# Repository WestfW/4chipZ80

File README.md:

# 4chipZ80
Z80 system using ATmega as IO/boot controller.  4 chips total.
---
This is a minimalist Z80 system based on a breadboard design by "Just4Fun" at hackaday.io:
https://hackaday.io/project/19000

My main contribution so far is the creation of a PCB, for a more permenant construction than the original breadboard.
This involved converting the printed schematic to an EAGLE version, as well as laying out the PCB. 

This project has won an **"Anything Goes" HackaDay prize** (for Just4Fun), and at this point has been built by a relatively impressive number of people in a rather impressive variety of different ways (not all of them using this PCB.)

The initial V1 PCB was sent for fabrication at PCBWAY.COM on 20170111.  It's been received, reviewed, and built (fully built as of 20170202), and it works, but it has some bugs:

 1. Short of I2C line to Ground plain.
 2. Missing pullup (IORQ) and pulldown (RESET) resistors.
 3. Rx/Tx swapped on serial connection.
 
Fixing these manually results in a working board.  It's not clear that the pull-resistors are needed.

There are now several versions of the EAGLE Schematic/PCB design posted here:

 1. Gerbers-v1bad.Z80-4chip-PCBWAY-BAD.\* - the design as sent to PCBWAY, complete with errors (except that the errors are "marked.")
With hand-done re-work, this design is known to work.  See the notes in the "To-Do" layer of the board, and the assorted "fix\*" files in that directory.
 1. Z80-4chip-v2.1.\* is the "corrected" design.  It has the fixes for the known bugs.  It also features a clarified (multi-sheet) schematic, *BUT* I have not personally fabbed or tested it, but several people on Hackaday.io have built V2 boards and say that they work.
 2. Z80-4chip-v3.\* Adds sockets for I2C EEPROM "Floppy Disks" that should permit use of CP/M and perhaps other Operating Systems.  Just4Fun has implemented the CP/M and QP/M BIOS and etc.  This has also not yet been fabbed or tested (but I have a volunteer!)  (Also Gerbers-V3/\* has pre-made geber files.)

I don't know if I'll be sending the "new" design(s) to actually be built.  A guy can only use so many Z80 boards, and I'm not up for being "in business."  I'll try to keep this update if other people use the design successfully.

Potential users may want to note that the original developer of the 4-chip Z80 system (Just4Fun) has published a new and improved version of the design that includes a PCB, at https://hackaday.io/project/159973

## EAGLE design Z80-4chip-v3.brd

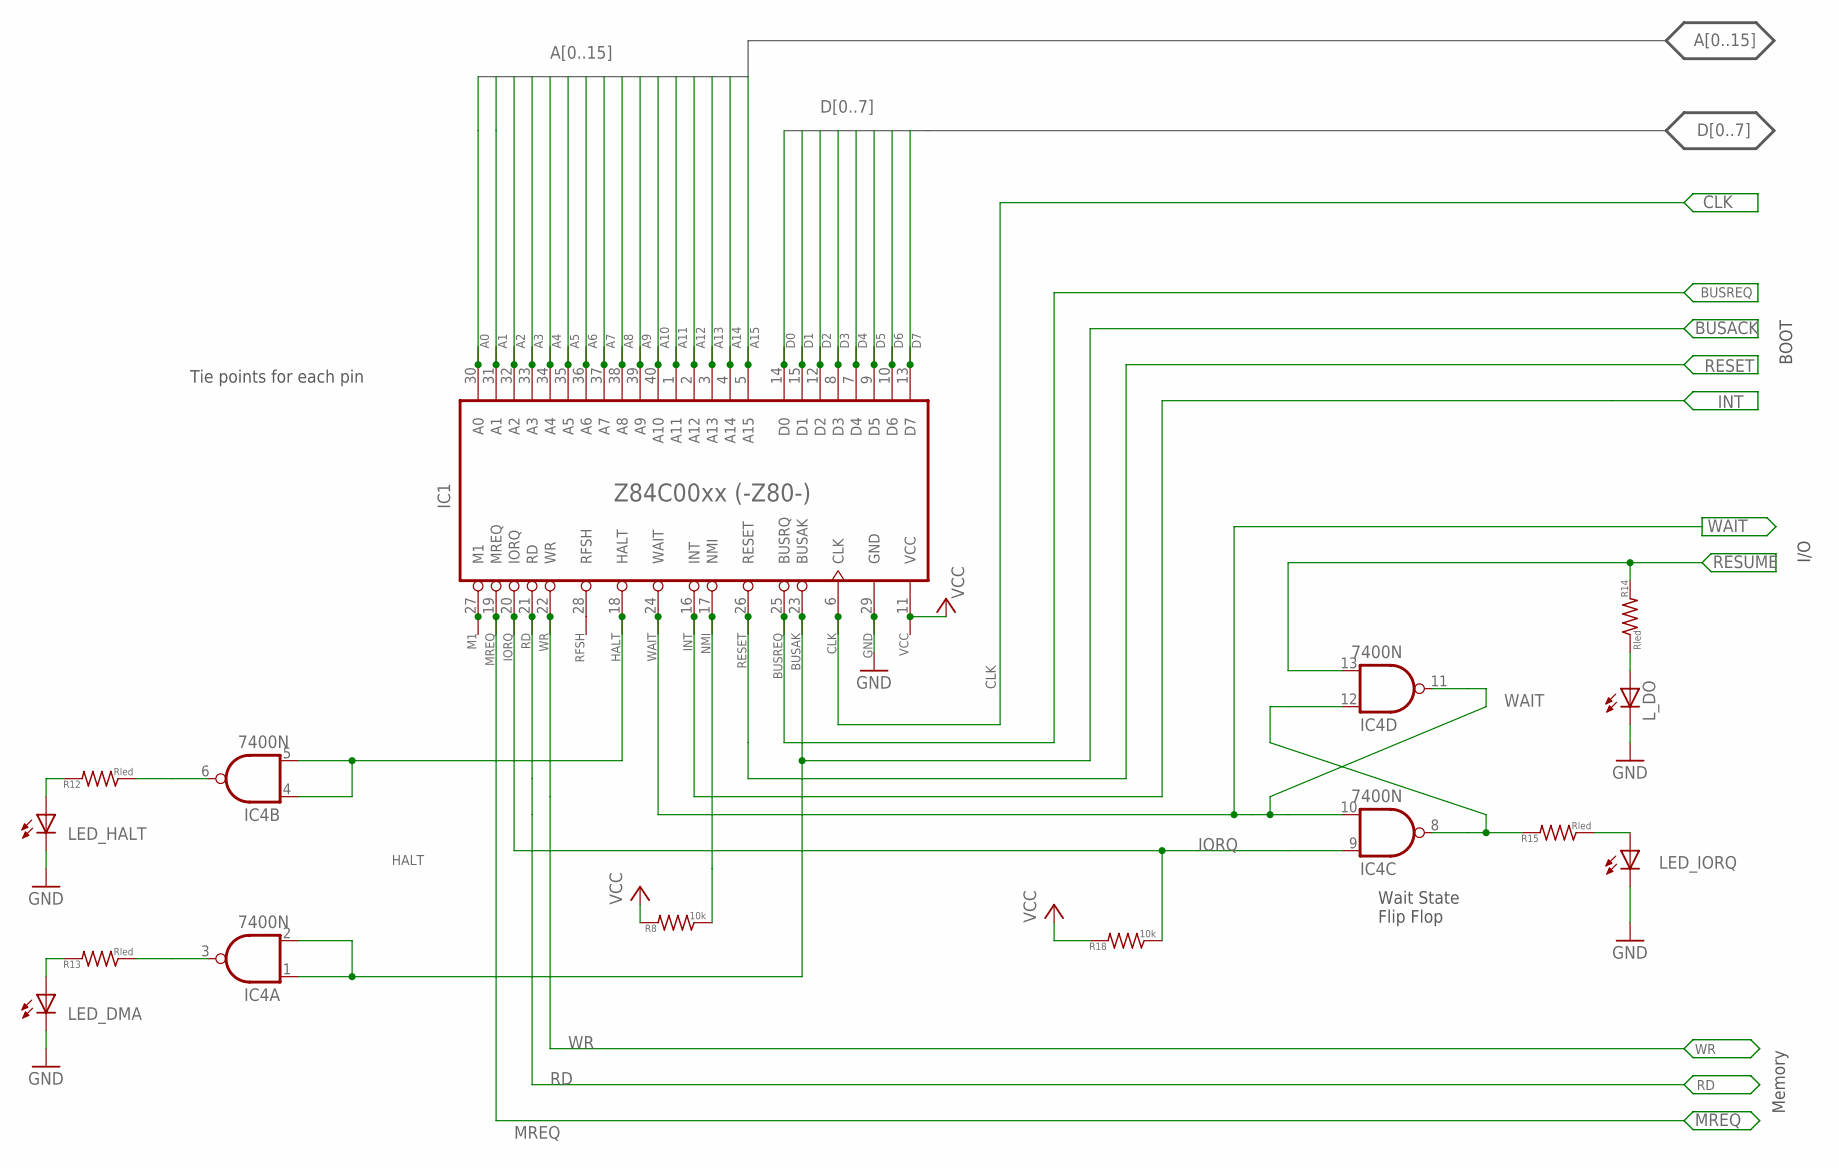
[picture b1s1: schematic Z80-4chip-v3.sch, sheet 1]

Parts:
A0, A1, A2, A3, A4, A5, A6, A7, A8, A9, A10, A11, A12, A13, A14, A15: WIRE-VIA8; VIA8
BUSAK: WIRE-VIA8; VIA8
BUSREQ: WIRE-VIA8; VIA8
CLK: WIRE-VIA8; VIA8
D0, D1, D2, D3, D4, D5, D6, D7: WIRE-VIA8; VIA8
GND: WIRE-VIA8; VIA8
HALT: WIRE-VIA8; VIA8
IC1: Z84C00xx (-Z80-); DIL40
IC4: 7400N; DIL14
INT: WIRE-VIA8; VIA8
IORQ: WIRE-VIA8; VIA8
LED_DMA: LED3MM
LED_HALT: LED3MM
LED_IORQ: LED3MM
L_DO: LED3MM
M1: WIRE-VIA8; VIA8
MREQ: WIRE-VIA8; VIA8
NMI: WIRE-VIA8; VIA8
R8, R18: 10k; 0204/5
R12, R13, R14, R15: Rled; 0204/5
RD: WIRE-VIA8; VIA8
RESET: WIRE-VIA8; VIA8
RFSH: WIRE-VIA8; VIA8
VCC: WIRE-VIA8; VIA8
WAIT: WIRE-VIA8; VIA8
WR: WIRE-VIA8; VIA8

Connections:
A0: A0.P$1, IC1.30 (A0); also elsewhere on the board
A1: A1.P$1, IC1.31 (A1); also elsewhere on the board
A2: A2.P$1, IC1.32 (A2); also elsewhere on the board
A3: A3.P$1, IC1.33 (A3); also elsewhere on the board
A4: A4.P$1, IC1.34 (A4); also elsewhere on the board
A5: A5.P$1, IC1.35 (A5); also elsewhere on the board
A6: A6.P$1, IC1.36 (A6); also elsewhere on the board
A7: A7.P$1, IC1.37 (A7); also elsewhere on the board
A8: A8.P$1, IC1.38 (A8); also elsewhere on the board
A9: A9.P$1, IC1.39 (A9); also elsewhere on the board
A10: A10.P$1, IC1.40 (A10); also elsewhere on the board
A11: A11.P$1, IC1.1 (A11); also elsewhere on the board
A12: A12.P$1, IC1.2 (A12); also elsewhere on the board
A13: A13.P$1, IC1.3 (A13); also elsewhere on the board
A14: A14.P$1, IC1.4 (A14); also elsewhere on the board
A15: A15.P$1, IC1.5 (A15); also elsewhere on the board
BUSACK: BUSAK.P$1, IC1.23 (BUSAK), IC4.1 (I0), IC4.2 (I1); also elsewhere on the board
BUSREQ: BUSREQ.P$1, IC1.25 (BUSRQ); also elsewhere on the board
CLK: CLK.P$1, IC1.6 (CLK); also elsewhere on the board
D0: D0.P$1, IC1.14 (D0); also elsewhere on the board
D1: D1.P$1, IC1.15 (D1); also elsewhere on the board
D2: D2.P$1, IC1.12 (D2); also elsewhere on the board
D3: D3.P$1, IC1.8 (D3); also elsewhere on the board
D4: D4.P$1, IC1.7 (D4); also elsewhere on the board
D5: D5.P$1, IC1.9 (D5); also elsewhere on the board
D6: D6.P$1, IC1.10 (D6); also elsewhere on the board
D7: D7.P$1, IC1.13 (D7); also elsewhere on the board
GND: GND.P$1, IC1.29 (GND), LED_DMA.K (C), LED_HALT.K (C), LED_IORQ.K (C), L_DO.K (C); also elsewhere on the board
HALT: HALT.P$1, IC1.18 (HALT), IC4.4 (I0), IC4.5 (I1)
INT: IC1.16 (INT), INT.P$1; also elsewhere on the board
IORQ: IC1.20 (IORQ), IC4.9 (I0), IORQ.P$1, R18.1
MREQ: IC1.19 (MREQ), MREQ.P$1; also elsewhere on the board
unnamed: IC1.27 (M1), M1.P$1
unnamed: IC4.6 (O), R12.1
unnamed: IC4.3 (O), R13.1
unnamed: LED_HALT.A, R12.2
unnamed: LED_DMA.A, R13.2
unnamed: L_DO.A, R14.1
unnamed: LED_IORQ.A, R15.1
unnamed: IC1.28 (RFSH), RFSH.P$1
unnamed: IC4.8 (O), IC4.12 (I0), R15.2
NMI: IC1.17 (NMI), NMI.P$1, R8.1
RD: IC1.21 (RD), RD.P$1; also elsewhere on the board
RESET: IC1.26 (RESET), RESET.P$1; also elsewhere on the board
RESUME: IC4.13 (I1), R14.2; also elsewhere on the board
VCC: IC1.11 (VCC), R8.2, R18.2, VCC.P$1; also elsewhere on the board
WAIT: IC1.24 (WAIT), IC4.10 (I1), IC4.11 (O), WAIT.P$1; also elsewhere on the board
WR: IC1.22 (WR), WR.P$1; also elsewhere on the board

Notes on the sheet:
Tie points for each pin
Memory
I/O
BOOT
Wait State Flip Flop

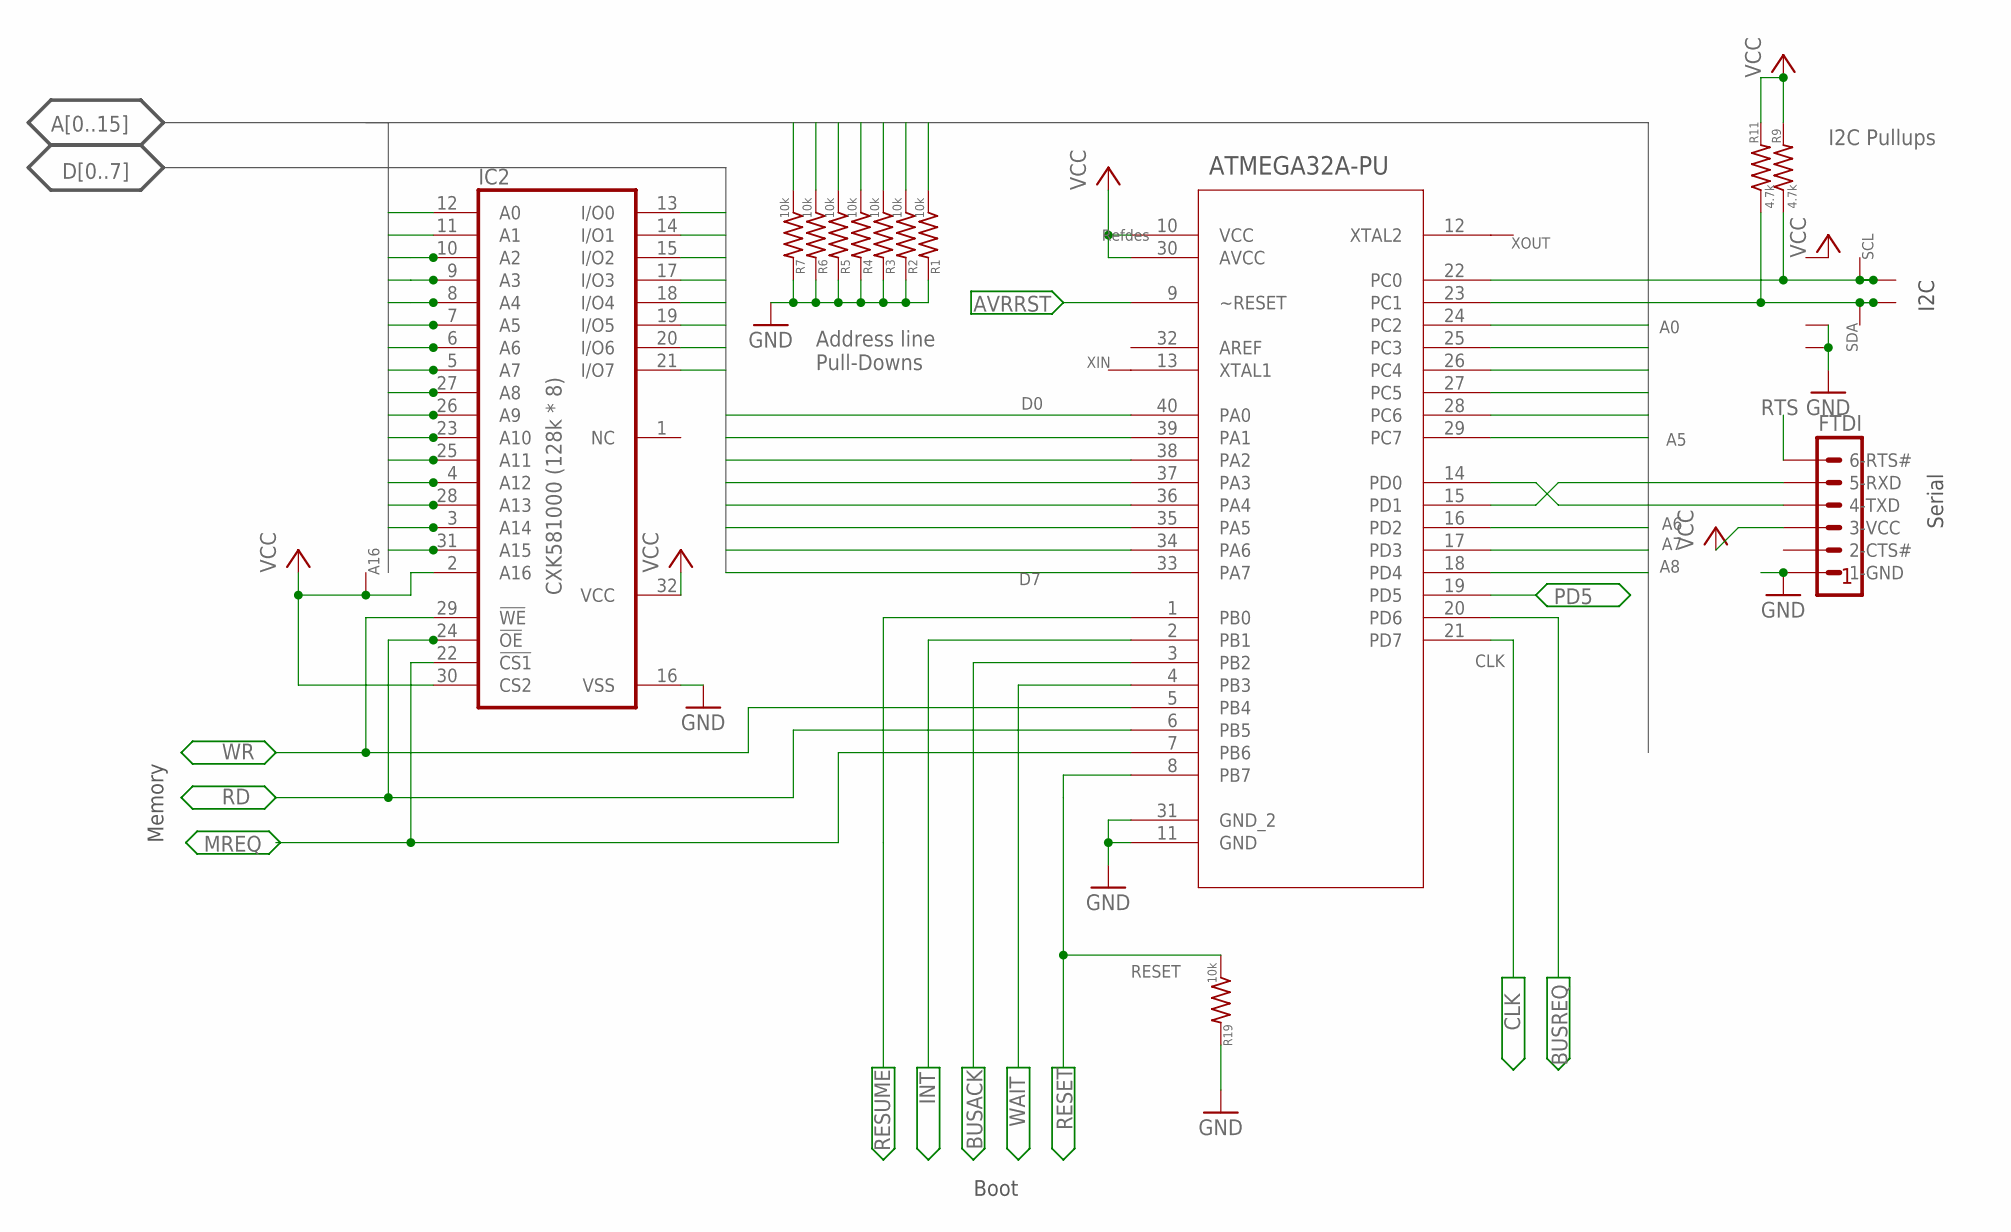
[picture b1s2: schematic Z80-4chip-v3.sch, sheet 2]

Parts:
A16: WIRE-VIA8; VIA8
FTDI: FTDI-TTL232R; MA06-1
I2CG, I2CGND, I2CV: WIRE-R10; VIA10
IC2: CXK581000 (128k * 8); DIL32
R1, R2, R3, R4, R5, R6, R7, R19: 10k; 0204/5
R9, R11: 4.7k; 0204/5
SCL: WIRE-R10; VIA10
SDA: WIRE-R10; VIA10
U1: ATMEGA32A-PU; DIP254P1524X482-40
W1, W2: WIRE-VIA8; VIA8
XIN: WIRE-VIA8; VIA8
XOUT: WIRE-VIA8; VIA8

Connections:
A0: IC2.12 (A0), U1.24 (PC2); also elsewhere on the board
A1: IC2.11 (A1), U1.25 (PC3); also elsewhere on the board
A2: IC2.10 (A2), U1.26 (PC4); also elsewhere on the board
A3: IC2.9 (A3), U1.27 (PC5); also elsewhere on the board
A4: IC2.8 (A4), U1.28 (PC6); also elsewhere on the board
A5: IC2.7 (A5), U1.29 (PC7); also elsewhere on the board
A6: IC2.6 (A6), U1.16 (PD2); also elsewhere on the board
A7: IC2.5 (A7), U1.17 (PD3); also elsewhere on the board
A8: IC2.27 (A8), U1.18 (PD4); also elsewhere on the board
A9: IC2.26 (A9), R1.1; also elsewhere on the board
A10: IC2.23 (A10), R2.1; also elsewhere on the board
A11: IC2.25 (A11), R3.1; also elsewhere on the board
A12: IC2.4 (A12), R4.1; also elsewhere on the board
A13: IC2.28 (A13), R5.1; also elsewhere on the board
A14: IC2.3 (A14), R6.1; also elsewhere on the board
A15: IC2.31 (A15), R7.1; also elsewhere on the board
AVRRST: U1.9 (~RESET); also elsewhere on the board
BUSACK: U1.3 (PB2); also elsewhere on the board
BUSREQ: U1.20 (PD6); also elsewhere on the board
CLK: U1.21 (PD7); also elsewhere on the board
D0: IC2.13 (I/O0), U1.40 (PA0); also elsewhere on the board
D1: IC2.14 (I/O1), U1.39 (PA1); also elsewhere on the board
D2: IC2.15 (I/O2), U1.38 (PA2); also elsewhere on the board
D3: IC2.17 (I/O3), U1.37 (PA3); also elsewhere on the board
D4: IC2.18 (I/O4), U1.36 (PA4); also elsewhere on the board
D5: IC2.19 (I/O5), U1.35 (PA5); also elsewhere on the board
D6: IC2.20 (I/O6), U1.34 (PA6); also elsewhere on the board
D7: IC2.21 (I/O7), U1.33 (PA7); also elsewhere on the board
GND: FTDI.1 (1-GND), I2CG.P$1, I2CGND.P$1, IC2.16 (VSS), R1.2, R2.2, R3.2, R4.2, R5.2, R6.2, R7.2, R19.2, U1.11 (GND), U1.31 (GND_2); also elsewhere on the board
INT: U1.2 (PB1); also elsewhere on the board
MREQ: IC2.22 (!CS1), U1.7 (PB6); also elsewhere on the board
unnamed: FTDI.5 (5-RXD), U1.15 (PD1)
unnamed: FTDI.4 (4-TXD), U1.14 (PD0)
unnamed: U1.13 (XTAL1), XIN.P$1
unnamed: U1.12 (XTAL2), XOUT.P$1
PD5: U1.19 (PD5); also elsewhere on the board
RD: IC2.24 (!OE), U1.6 (PB5); also elsewhere on the board
RESET: R19.1, U1.8 (PB7); also elsewhere on the board
RESUME: U1.1 (PB0); also elsewhere on the board
RTS: FTDI.6 (6-RTS#); also elsewhere on the board
SCL: R9.1, SCL.P$1, U1.22 (PC0), W1.P$1; also elsewhere on the board
SDA: R11.1, SDA.P$1, U1.23 (PC1), W2.P$1; also elsewhere on the board
VCC: A16.P$1, FTDI.3 (3-VCC), I2CV.P$1, IC2.2 (A16), IC2.30 (CS2), IC2.32 (VCC), R9.2, R11.2, U1.10 (VCC), U1.30 (AVCC); also elsewhere on the board
WAIT: U1.4 (PB3); also elsewhere on the board
WR: IC2.29 (!WE), U1.5 (PB4); also elsewhere on the board

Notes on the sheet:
I2C Pullups
Address line Pull-Downs
I2C
Memory
Boot
Serial

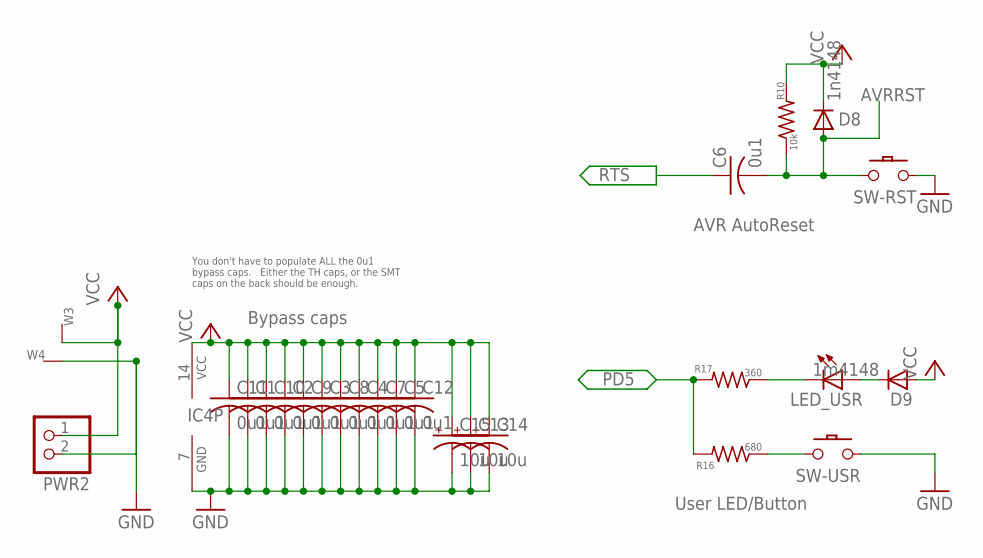
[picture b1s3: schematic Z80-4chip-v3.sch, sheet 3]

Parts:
C1, C2, C3, C4, C5, C6, C7: 0u1; C050-024X044
C8, C9, C10, C11, C12: 0u1; C1206
C13, C14, C15: 10u; E2,5-6
D8: 1n4148; DO35-5
D9: 1m4148; DO35-5
IC4: 7400N; DIL14
LED_USR: LED3MM
PWR2: JST_2PIN-THM; JST-PH-2-THM
R10: 10k; 0204/5
R16: 680; 0204/5
R17: 360; 0204/5
SW-RST: SW-PB2/; SW-PB
SW-USR: SW-PB2L; SW-PB
W3, W4: WIRE-R10; VIA10

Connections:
AVRRST: C6.2, D8.A, R10.1, SW-RST.3; also elsewhere on the board
GND: C1.2, C2.2, C3.2, C4.2, C5.2, C7.2, C8.2, C9.2, C10.2, C11.2, C12.2, C13.-, C14.-, C15.-, IC4.7 (GND), PWR2.2 (1), SW-RST.2, SW-RST.5 (GND), SW-USR.2, SW-USR.5 (GND), W4.P$1; also elsewhere on the board
unnamed: LED_USR.K (C), R17.1
unnamed: D9.C, LED_USR.A
unnamed: R16.1, SW-USR.4
PD5: R16.2, R17.2; also elsewhere on the board
RTS: C6.1; also elsewhere on the board
VCC: C1.1, C2.1, C3.1, C4.1, C5.1, C7.1, C8.1, C9.1, C10.1, C11.1, C12.1, C13.+, C14.+, C15.+, D8.C, D9.A, IC4.14 (VCC), PWR2.1 (2), R10.2, W3.P$1; also elsewhere on the board

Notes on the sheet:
Bypass caps
You don't have to populate ALL the 0u1 bypass caps. Either the TH caps, or the SMT caps on the back should be enough.
AVR AutoReset
User LED/Button

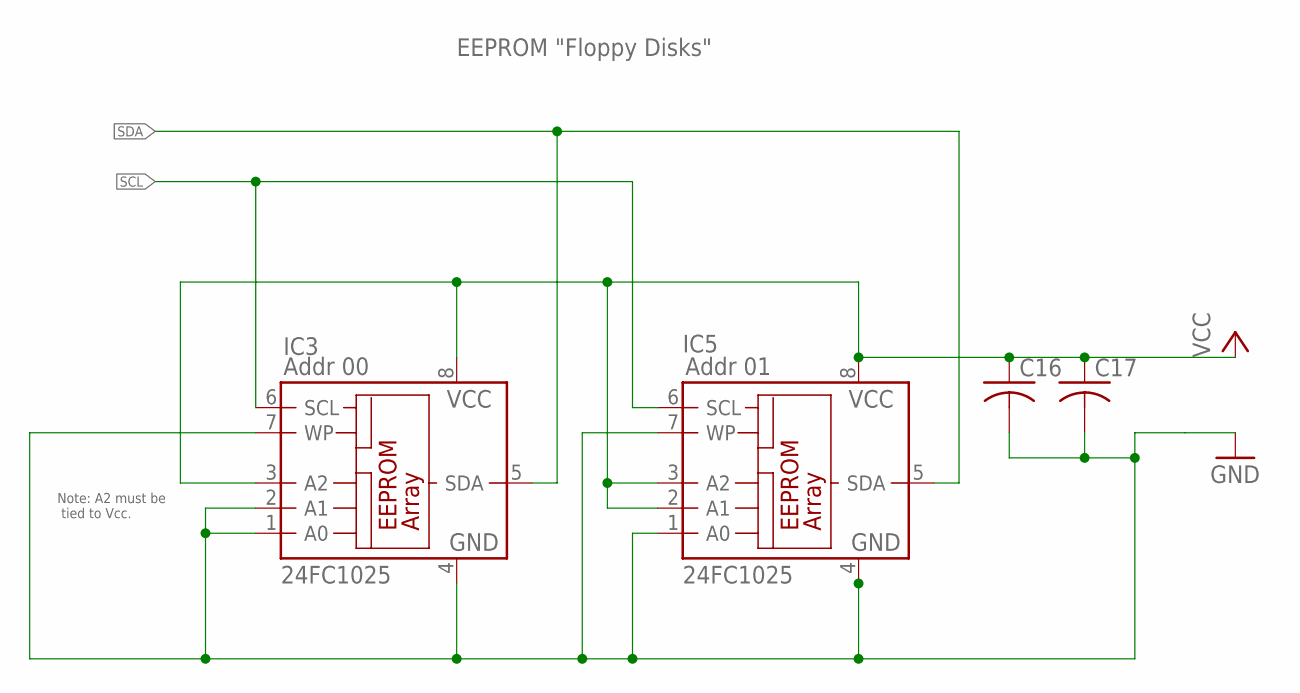
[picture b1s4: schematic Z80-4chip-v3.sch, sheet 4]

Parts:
C16, C17: C-US-5MM; C050-024X044
IC3, IC5: 24FC1025; DIL8

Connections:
GND: C16.2, C17.2, IC3.1 (A0), IC3.2 (A1), IC3.4 (GND), IC3.7 (WP), IC5.1 (A0), IC5.4 (GND), IC5.7 (WP); also elsewhere on the board
SCL: IC3.6 (SCL), IC5.6 (SCL); also elsewhere on the board
SDA: IC3.5 (SDA), IC5.5 (SDA); also elsewhere on the board
VCC: C16.1, C17.1, IC3.3 (A2), IC3.8 (VCC), IC5.2 (A1), IC5.3 (A2), IC5.8 (VCC); also elsewhere on the board

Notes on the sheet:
Addr 00
Addr 01
EEPROM "Floppy Disks"
Note: A2 must be tied to Vcc.

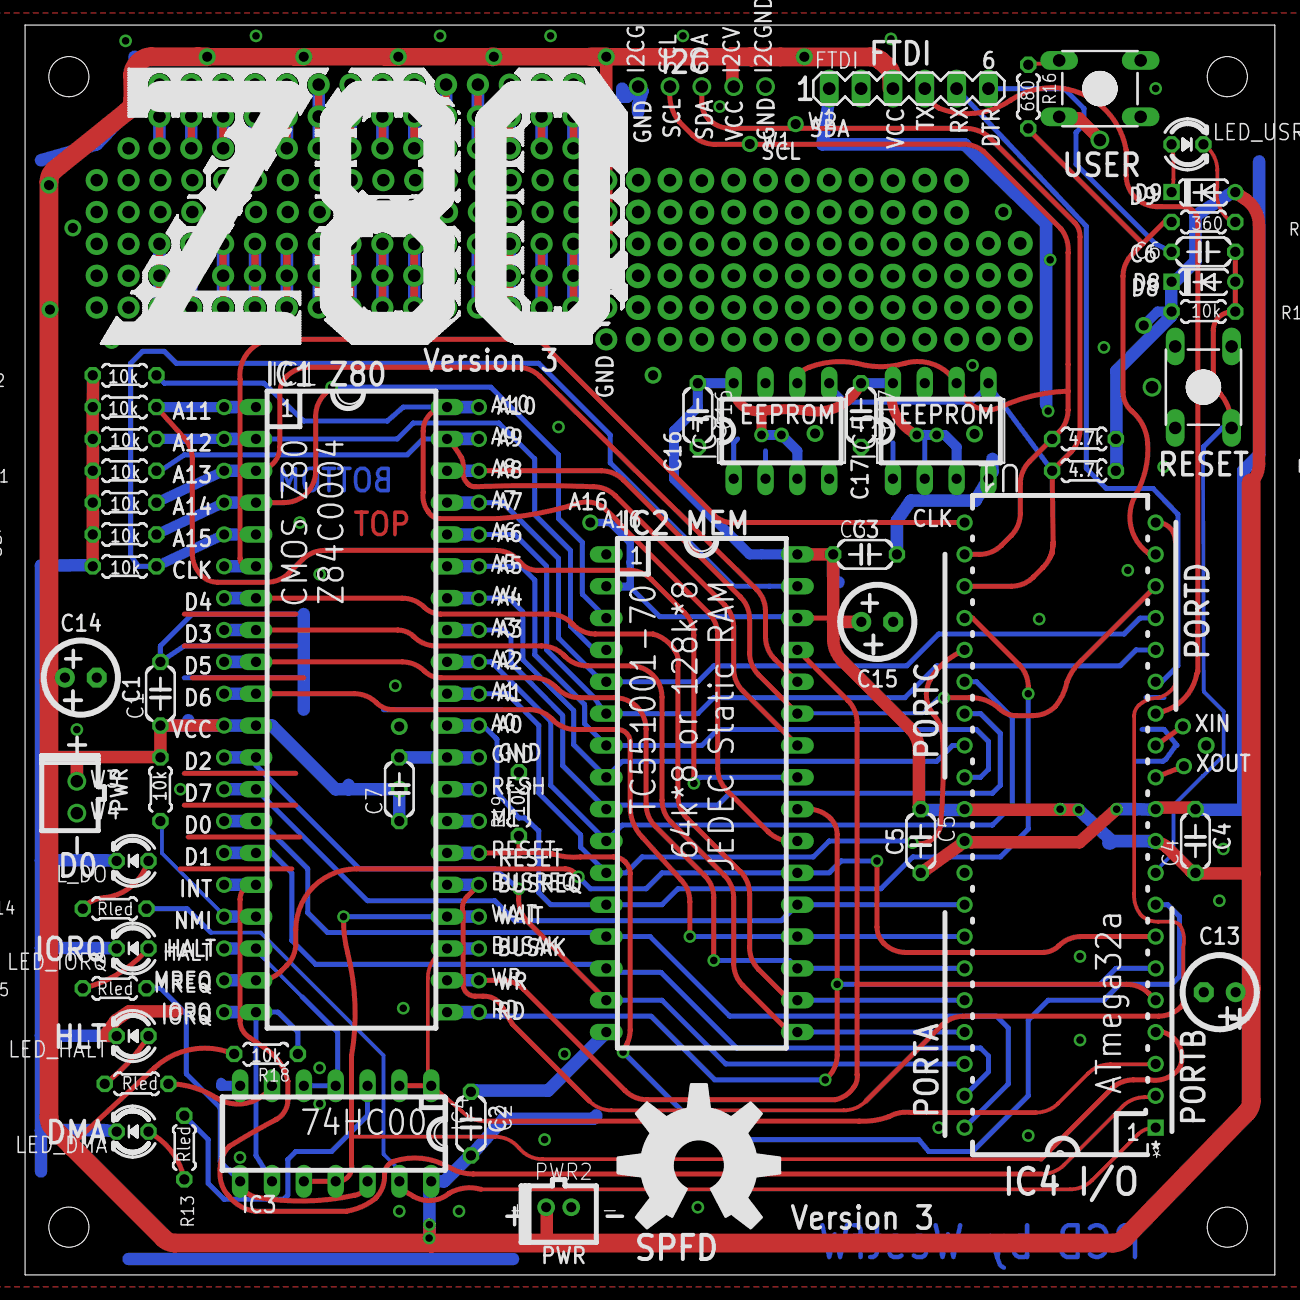
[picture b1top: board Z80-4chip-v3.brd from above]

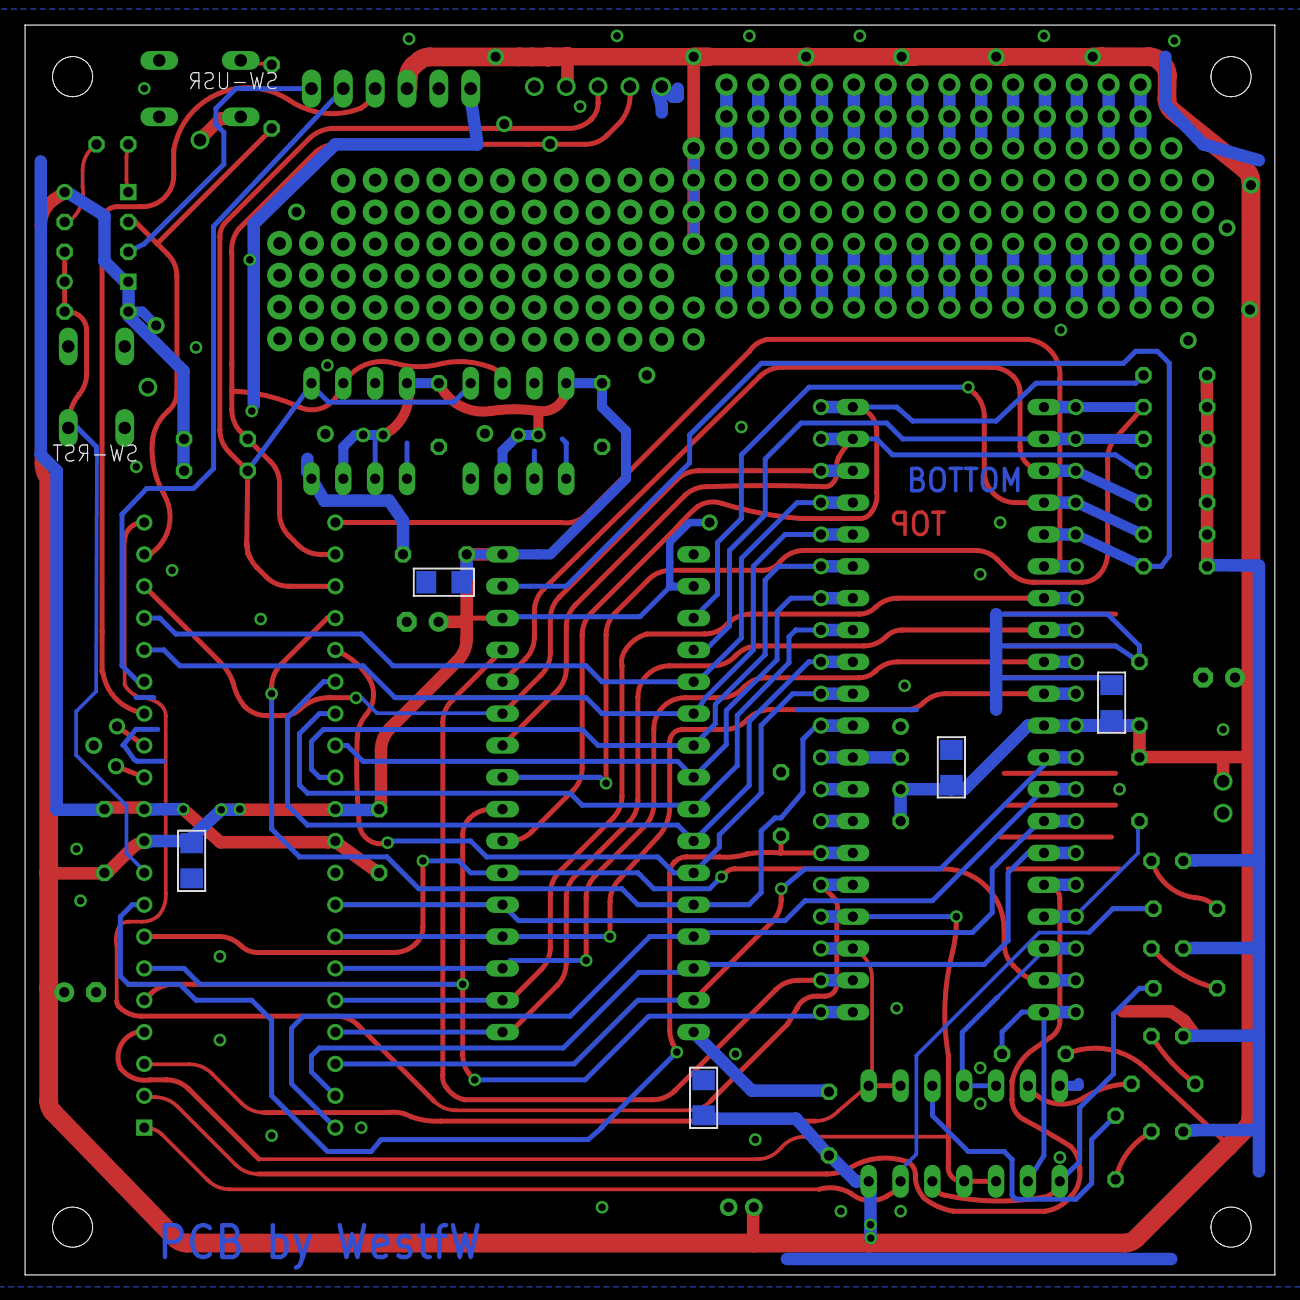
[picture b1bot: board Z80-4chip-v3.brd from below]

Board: 2 copper layers, 99.7 x 99.7 mm, 105 parts (5 on the bottom side), 60 nets.

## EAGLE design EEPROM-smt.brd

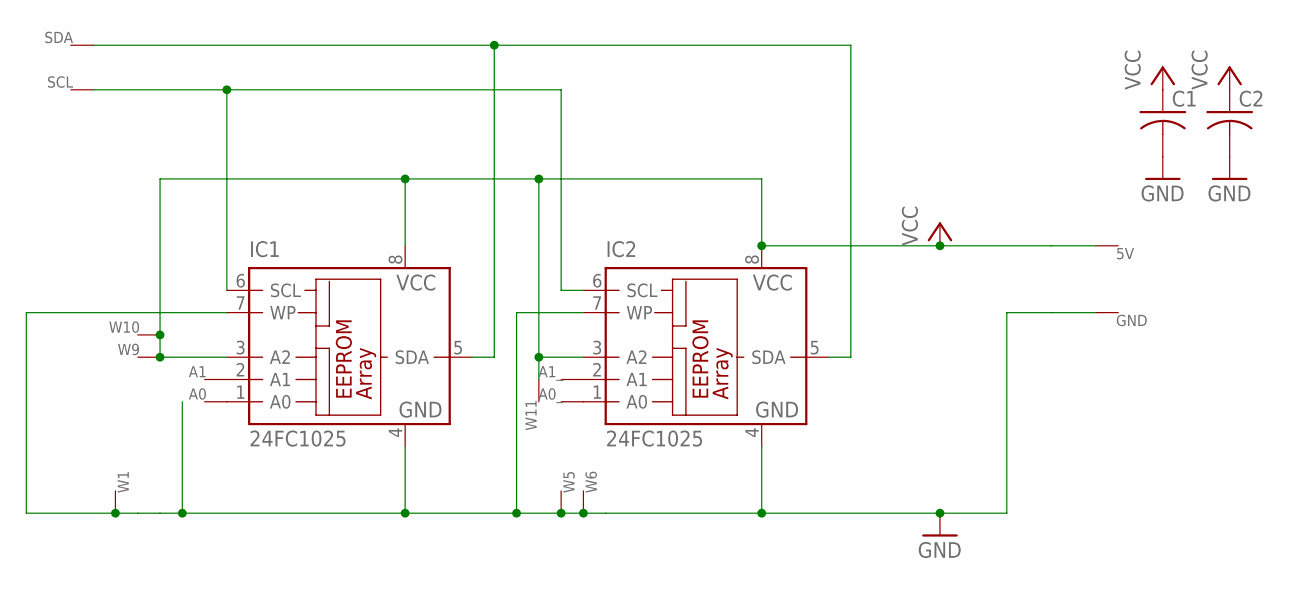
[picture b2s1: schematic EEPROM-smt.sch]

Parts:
5V: WIRE-VIA8; VIA8
A0, A0_, A1, A1_: WIRE-R6; VIA6
C1, C2: C-USC0805; C0805
GND: WIRE-VIA8; VIA8
IC1, IC2: 24FC1025; SO-08
SCL: WIRE-VIA8; VIA8
SDA: WIRE-VIA8; VIA8
W1, W5, W6, W9, W10, W11: WIRE-VIA8; VIA8

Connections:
GND: C1.2, C2.2, GND.P$1, IC1.4 (GND), IC1.7 (WP), IC2.4 (GND), IC2.7 (WP), W1.P$1, W5.P$1, W6.P$1
unnamed: A1.P$1, IC1.2 (A1)
unnamed: A0.P$1, IC1.1 (A0)
unnamed: IC1.6 (SCL), IC2.6 (SCL), SCL.P$1
unnamed: IC1.5 (SDA), IC2.5 (SDA), SDA.P$1
unnamed: A1_.P$1, IC2.2 (A1)
unnamed: A0_.P$1, IC2.1 (A0)
VCC: 5V.P$1, C1.1, C2.1, IC1.3 (A2), IC1.8 (VCC), IC2.3 (A2), IC2.8 (VCC), W9.P$1, W10.P$1, W11.P$1

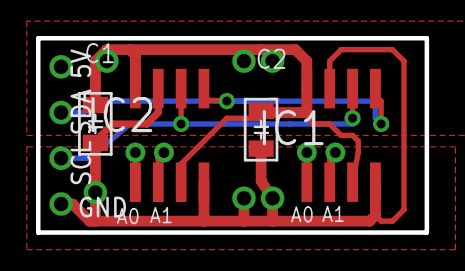
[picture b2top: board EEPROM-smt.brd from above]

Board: 2 copper layers, 21.6 x 10.8 mm, 18 parts (0 on the bottom side), 8 nets.

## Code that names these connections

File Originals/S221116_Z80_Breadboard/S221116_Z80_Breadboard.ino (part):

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//
// ------------------------------------------------------------------------------

#define   D0          24  // PA0 pin 40   Z80 data bus
#define   D1          25  // PA1 pin 39
#define   D2          26  // PA2 pin 38
#define   D3          27  // PA3 pin 37
#define   D4          28  // PA4 pin 36
#define   D5          29  // PA5 pin 35
#define   D6          30  // PA6 pin 34
#define   D7          31  // PA7 pin 33

#define   AD0         18  // PC2 pin 24   Z80 address bus (AD0-AD8 = A0-A8 on A04113 schematic)
#define   AD1         19  // PC3 pin 25
#define   AD2         20  // PC4 pin 26
#define   AD3         21  // PC5 pin 27
#define   AD4         22  // PC6 pin 28
#define   AD5         23  // PC7 pin 29
#define   AD6         10  // PD2 pin 16
#define   AD7         11  // PD3 pin 17
#define   AD8         12  // PD4 pin 18

#define   INT_         1  // PB1 pin 2    Z80 control bus
#define   BUSACK_      2  // PB2 pin 3
#define   WAIT_        3  // PB3 pin 4
#define   WR_          4  // PB4 pin 5
#define   RD_          5  // PB5 pin 6
#define   MREQ_        6  // PB6 pin 7
#define   RESET_       7  // PB7 pin 8
#define   BUSREQ_     14  // PD6 pin 20
#define   CLK         15  // PD7 pin 21

#define   SCL_PC0     16  // PC0 pin 22   IOEXP connector
#define   SDA_PC1     17  // PC1 pin 23

#define   LED_D0       0  // PB0 pin 1    Led LED_0 ON if HIGH
#define   WAIT_RES_    0  // PB0 pin 1    Internal control line
#define   USER        13  // PD5 pin 19   Led USER and key

// ------------------------------------------------------------------------------
//
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  pinMode(RESET_, OUTPUT);                        // Configure RESET_ and set it ACTIVE
  digitalWrite(RESET_, LOW);

  pinMode(WAIT_RES_, OUTPUT);                     // Configure WAIT_RES_ and set it ACTIVE to reset the WAIT FF (U1C)
  digitalWrite(WAIT_RES_, LOW);

  pinMode(USER, OUTPUT);                          // USER led OFF
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  pinMode(BUSREQ_, OUTPUT);
  digitalWrite(BUSREQ_, HIGH);
  
  DDRA = 0x00;                                    // Configure Z80 data bus D0-D7 (PA0-PA7) as input with pull-up
  PORTA = 0xFF;
  DDRC = DDRC & B00000011;                        // Configure Z80 address bus AD0-AD5 (PC2-PC7) as input with pull-up
  PORTC = PORTC | B11111100;
  DDRD = DDRD & B11100011;                        // Configure Z80 address bus AD6-AD8 (PD2-PD4) as input with pull-up
  PORTD = PORTD | B00011100;
  pinMode(MREQ_, INPUT_PULLUP);                   // Configure MREQ_ as input with pull-up
  pinMode(RD_, INPUT_PULLUP);                     // Configure RD_ as input with pull-up
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      Serial.println();
    }

    DDRA = 0xFF;                                  // Configure Z80 data bus D0-D7 (PA0-PA7) as output
    PORTA = data;                                 // Current output on data bus
    DDRC = DDRC | B11111100;                      // Configure Z80 address bus AD0-AD5 (PC2-PC7) as output
    DDRD = DDRD | B00011100;                      // Configure Z80 address bus AD6-AD8 (PD2-PD4) as output
    PORTC = (PORTC & B00000011) | ((lowByte(address) << 2) & B11111100);  // Output address AD0-AD5 (PC2-PC7)
    PORTD = (PORTD & B11100011) | (byte(address >> 4 ) & B00011100);      // Output address AD6-AD8 (PD2-PD4)
    //PORTC = (PORTC & B11111101) | ((highByte(address) & B00000100) >> 1); // Output address AD10 (PC1)
    digitalWrite(MREQ_, LOW);                     // Enable external RAM /CE1 pin
    digitalWrite(WR_, LOW);                       // Write data into current address of the external RAM (10us 1-0-1 pulse)
    digitalWrite(WR_, HIGH);
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  pinMode(RD_, INPUT_PULLUP);                     // Configure RD_ as input with pull-up
  pinMode(RD_, INPUT);
  pinMode(MREQ_, INPUT_PULLUP);                   // Configure MREQ_ as input with pull-up
  DDRA = 0x00;                                    // Configure Z80 data bus D0-D7 (PA0-PA7) as input with pull-up
  PORTA = 0xFF;
  DDRC = DDRC & B00000011;                        // Configure Z80 address bus AD0-AD5 (PC2-PC7) as input with pull-up
  PORTC = PORTC | B11111100;
  DDRD = DDRD & B11100011;                        // Configure Z80 address bus AD6-AD8 (PD2-PD4) as input with pull-up
  PORTD = PORTD | B00011100;
  digitalWrite(RESET_, LOW);                      // Activate Z80 RESET_ signal
  digitalWrite(BUSREQ_, HIGH);                    // Release Z80 from DMA
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    if (!digitalRead(WR_))
    // IO WRITE operation requested
    {
      ioAddress = PINC >> 2;                      // Read Z80 address bus AD0-AD5 (PC2-PC7)
      ioAddress = (ioAddress & B00111111) | ((PIND << 4) & B11000000);  // Read Z80 address bus AD6-AD7 (PD2-PD3)
      ioData = PINA;                              // Read Z80 data bus D0-D7 (PA0-PA7)

      if (debugLev > 1)
      {
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      if (!digitalRead(RD_))
      // IO READ operation requested
      {
        ioAddress = PINC >> 2;                    // Read Z80 address bus AD0-AD5 (PC2-PC7)
        ioAddress = (ioAddress & B00111111) | ((PIND << 4) & B11000000); // Read Z80 address bus AD6-AD7 (PD2-PD3)
        switch (ioAddress)
        // Execute the requested I/O READ operation
        {
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          Serial.println();        
        }
        
        DDRA = 0xFF;                               // Configure Z80 data bus D0-D7 (PA0-PA7) as output
        PORTA = ioData;                            // Current output on data bus
        
        digitalWrite(BUSREQ_, LOW);                // Request for a DMA
        digitalWrite(WAIT_RES_, LOW);              // Now is safe reset WAIT FF (exiting from WAIT state)

        delayMicroseconds(2);                      // Wait 2us just to be sure that Z80 read the data
        DDRA = 0x00;                               // Configure Z80 data bus D0-D7 (PA0-PA7) as input with pull-up
        PORTA = 0xFF;

        digitalWrite(WAIT_RES_, HIGH);             // Now Z80 is in DMA, so it's safe set WAIT_RES_ HIGH again
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
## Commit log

2017-01-31 First commit: 4chipZ80
2017-01-31 Add a picture.
2017-01-31 Add a pic to document V1 PCB errors and fixes.
2017-02-03 Photo of IORQ pull-up fix
2017-02-03 capitalize filename consistantly
2017-02-03 Add the .brd and .sch with mistakes that were made to work, so that people who wind up with such boards can refer to them.
2017-02-04 Board/sch with bugs "fixed." Not yet fabbed or tested.
2017-02-04 README for Gerbers-v1bad
2017-02-06 Initial commit of "loader"; the expanded version of m32 "sketch" that services the Z80. This should be identical to Just4Fun's version
2017-02-06 Change "RTS" to "DTR" on silkscreen
2017-02-08 Move text to tPlace for more standard usage.
2017-02-11 Initial version of working fig-Forth for 8080/Z80
2017-02-18 Clone "loader" from S221116_R230117_Z80.ino
2017-04-22 Mod silkscreen: RTS->DTR, add "Version 2." Generate Gerbers-V2.
2017-05-26 Modify Z80 brd to include power/gnd vias near prototype area. Add (untested) board designs for EEPROM floppy-emulation module.
2017-11-15 Add VCC/GND labels to bottom silk for new prototype-area vias. Bump version to V2.1 to account for the new power vias in prototype area. rename files to reflect version number (Z80-4chip-v2.1.*) Add 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
2017-11-15 New picture.
2018-01-20 Initial commit of "version 3" This adds I2C EEPROM chips for CP/M compatibility. (but the prototyping area is decreased and part becomes just sea-of-pads.)
2018-01-20 Slight adjustment to BSilk near EEPROMs; take Vcc labels off of vias.
2018-01-20 oops; a bit of extra trash on bottom layer silkscreen.
2018-01-20 Add directory and gerbv project for V3 Gerbers
2018-01-20 Move (and duplicate) the "version" text so it's not obscured by vias.
2018-01-20 Add gerbers for v3
2018-01-20 Update the README file: filename changes. V2 has been successfully built by others. add V3. Mention the HackaDay Prize-winning status
2018-02-04 readme.md
